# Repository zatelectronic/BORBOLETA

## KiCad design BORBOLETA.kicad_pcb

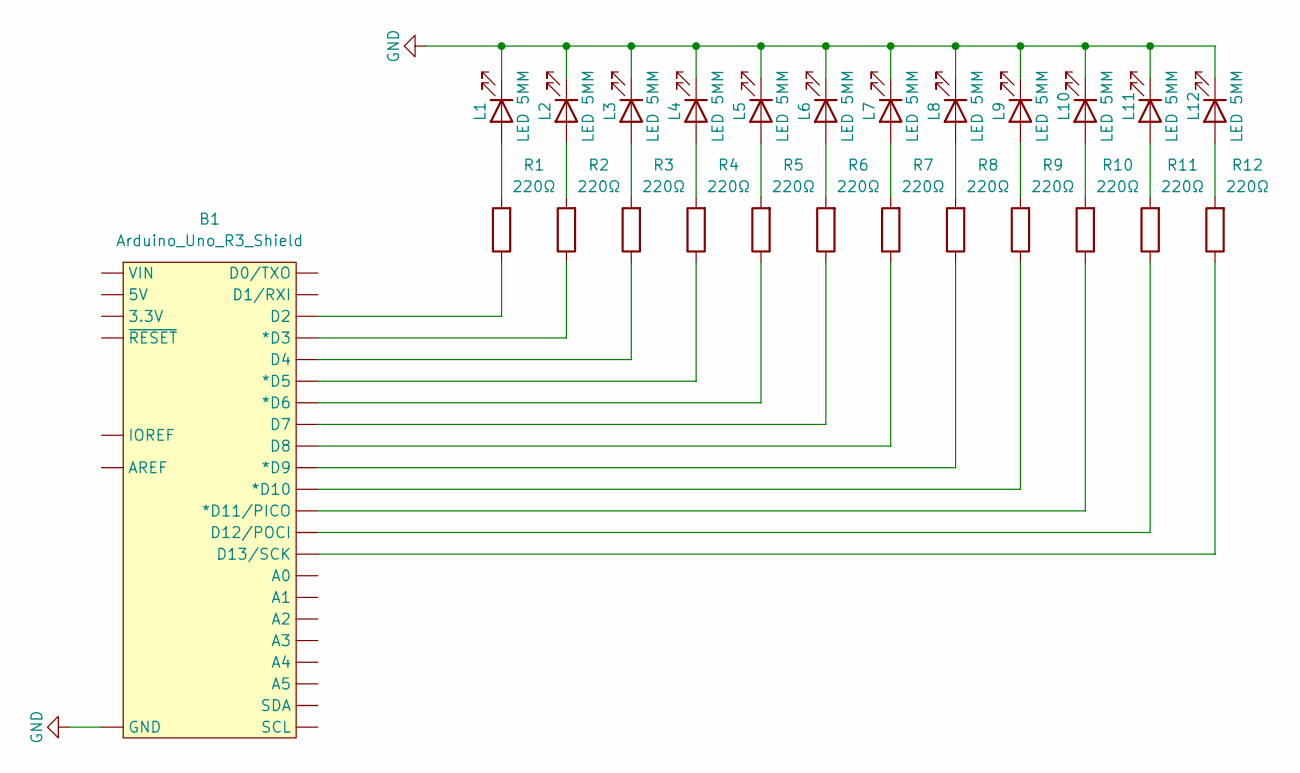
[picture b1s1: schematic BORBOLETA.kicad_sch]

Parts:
B1: Arduino_Uno_R3_Shield; Uno_R3_Shield_NoLabels
L1, L2, L3, L4, L5, L6, L7, L8, L9, L10, L11, L12: LED 5MM; LED_D5.0mm
R1, R2, R3, R4, R5, R6, R7, R8, R9, R10, R11, R12: 220Ω; R_Axial_DIN0204_L3.6mm_D1.6mm_P7.62mm_Horizontal

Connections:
GND: B1.GND, L1.1 (K), L2.1 (K), L3.1 (K), L4.1 (K), L5.1 (K), L6.1 (K), L7.1 (K), L8.1 (K), L9.1 (K), L10.1 (K), L11.1 (K), L12.1 (K)
unnamed: B1.D3 (*D3), R2.1
unnamed: B1.D5 (*D5), R4.1
unnamed: B1.D6 (*D6), R5.1
unnamed: B1.D9 (*D9), R8.1
unnamed: B1.D10 (*D10), R9.1
unnamed: B1.D11 (*D11/PICO), R10.1
unnamed: B1.D12 (D12/POCI), R11.1
unnamed: B1.D13 (D13/SCK), R12.1
unnamed: B1.D2, R1.1
unnamed: B1.D4, R3.1
unnamed: B1.D7, R6.1
unnamed: B1.D8, R7.1
unnamed: L1.2 (A), R1.2
unnamed: L2.2 (A), R2.2
unnamed: L3.2 (A), R3.2
unnamed: L4.2 (A), R4.2
unnamed: L5.2 (A), R5.2
unnamed: L6.2 (A), R6.2
unnamed: L7.2 (A), R7.2
unnamed: L8.2 (A), R8.2
unnamed: L9.2 (A), R9.2
unnamed: L10.2 (A), R10.2
unnamed: L11.2 (A), R11.2
unnamed: L12.2 (A), R12.2

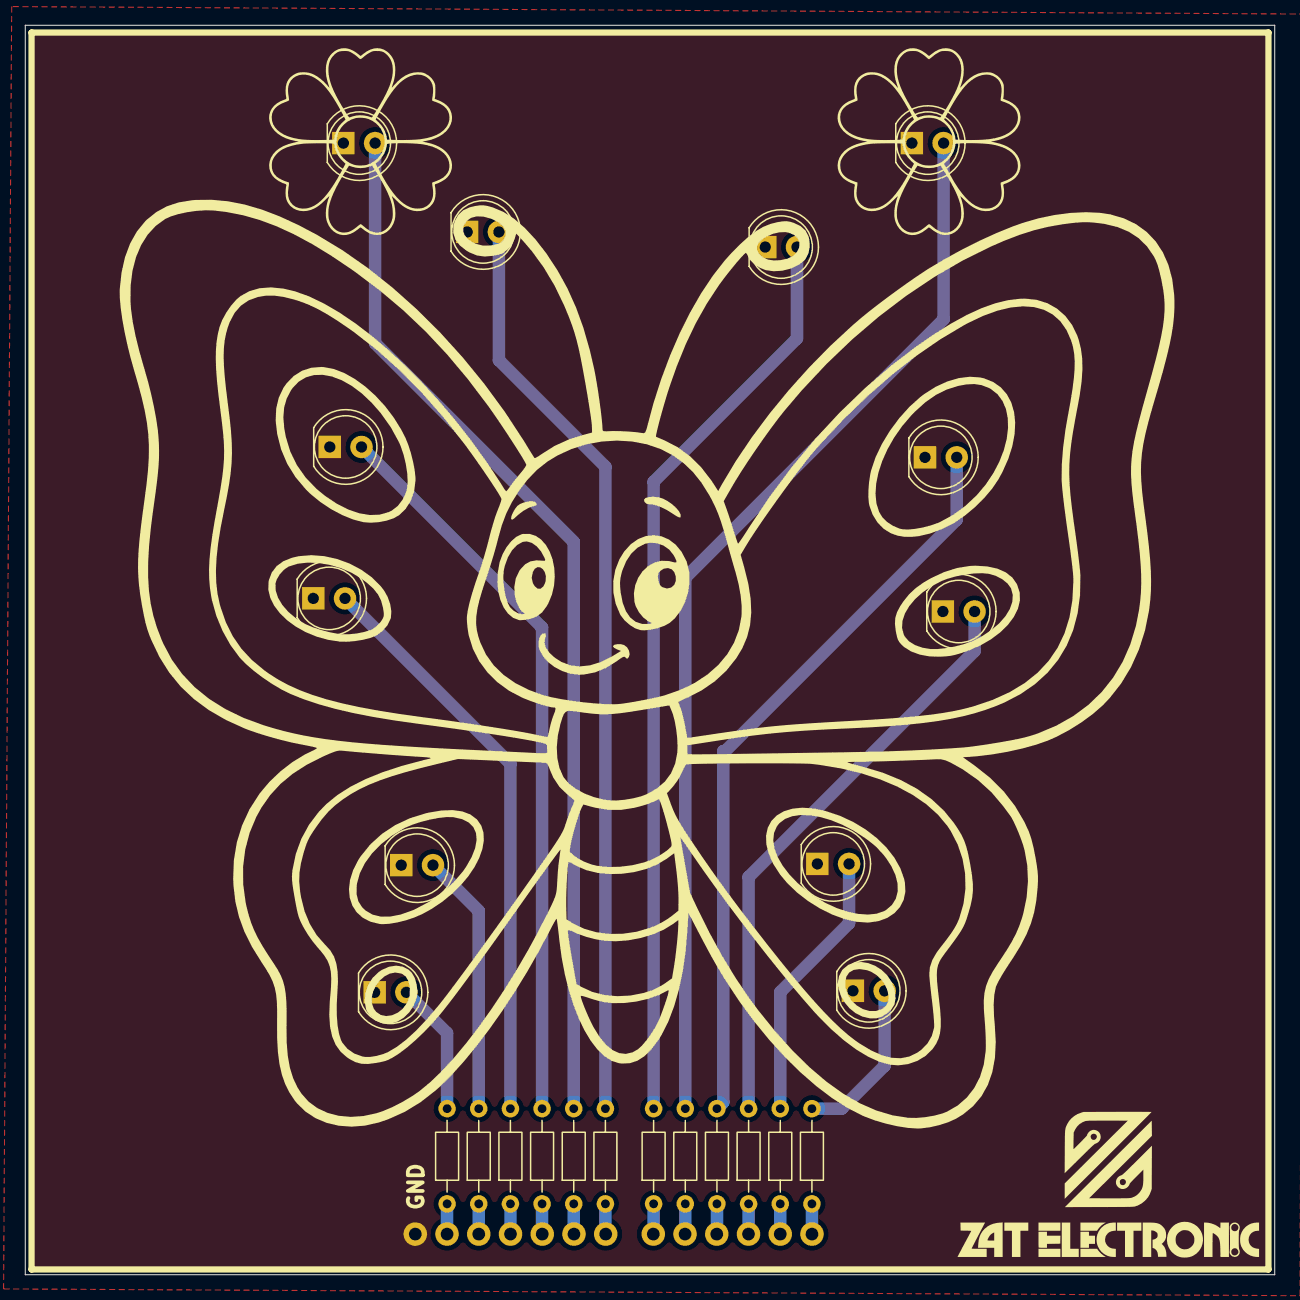
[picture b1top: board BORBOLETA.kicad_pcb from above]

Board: 2 copper layers, 100.0 x 100.0 mm, 25 parts (0 on the bottom side), 25 nets.

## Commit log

2026-06-28 commit_3
